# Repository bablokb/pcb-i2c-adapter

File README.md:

pcb-i2c-adapter
===============

This is a small PCB mapping various I2C pin combinations to a Grove connector.

Useful to connect all kinds of I2C-breakouts using Grove. Since every
breakout uses it's own pin-order, the PCB supports eight different
variations (additionally the Pi-variant: with 
pins 1 (3V3), 3 (SDA), 5 (SCL), 7 (nc), 9 (GND)).

KiCAD design-files are in the subdirectory `pcb-i2c-adapter`.

Production files for JLCPCB are in `production_files/`.

License
-------

[![CC BY-SA 4.0][cc-by-sa-shield]][cc-by-sa]

This work is licensed under a
[Creative Commons Attribution-ShareAlike 4.0 International
License][cc-by-sa].

[![CC BY-SA 4.0][cc-by-sa-image]][cc-by-sa]

[cc-by-sa]: http://creativecommons.org/licenses/by-sa/4.0/
[cc-by-sa-image]: https://licensebuttons.net/l/by-sa/4.0/88x31.png
[cc-by-sa-shield]:
https://img.shields.io/badge/License-CC%20BY--SA%204.0-lightgrey.svg

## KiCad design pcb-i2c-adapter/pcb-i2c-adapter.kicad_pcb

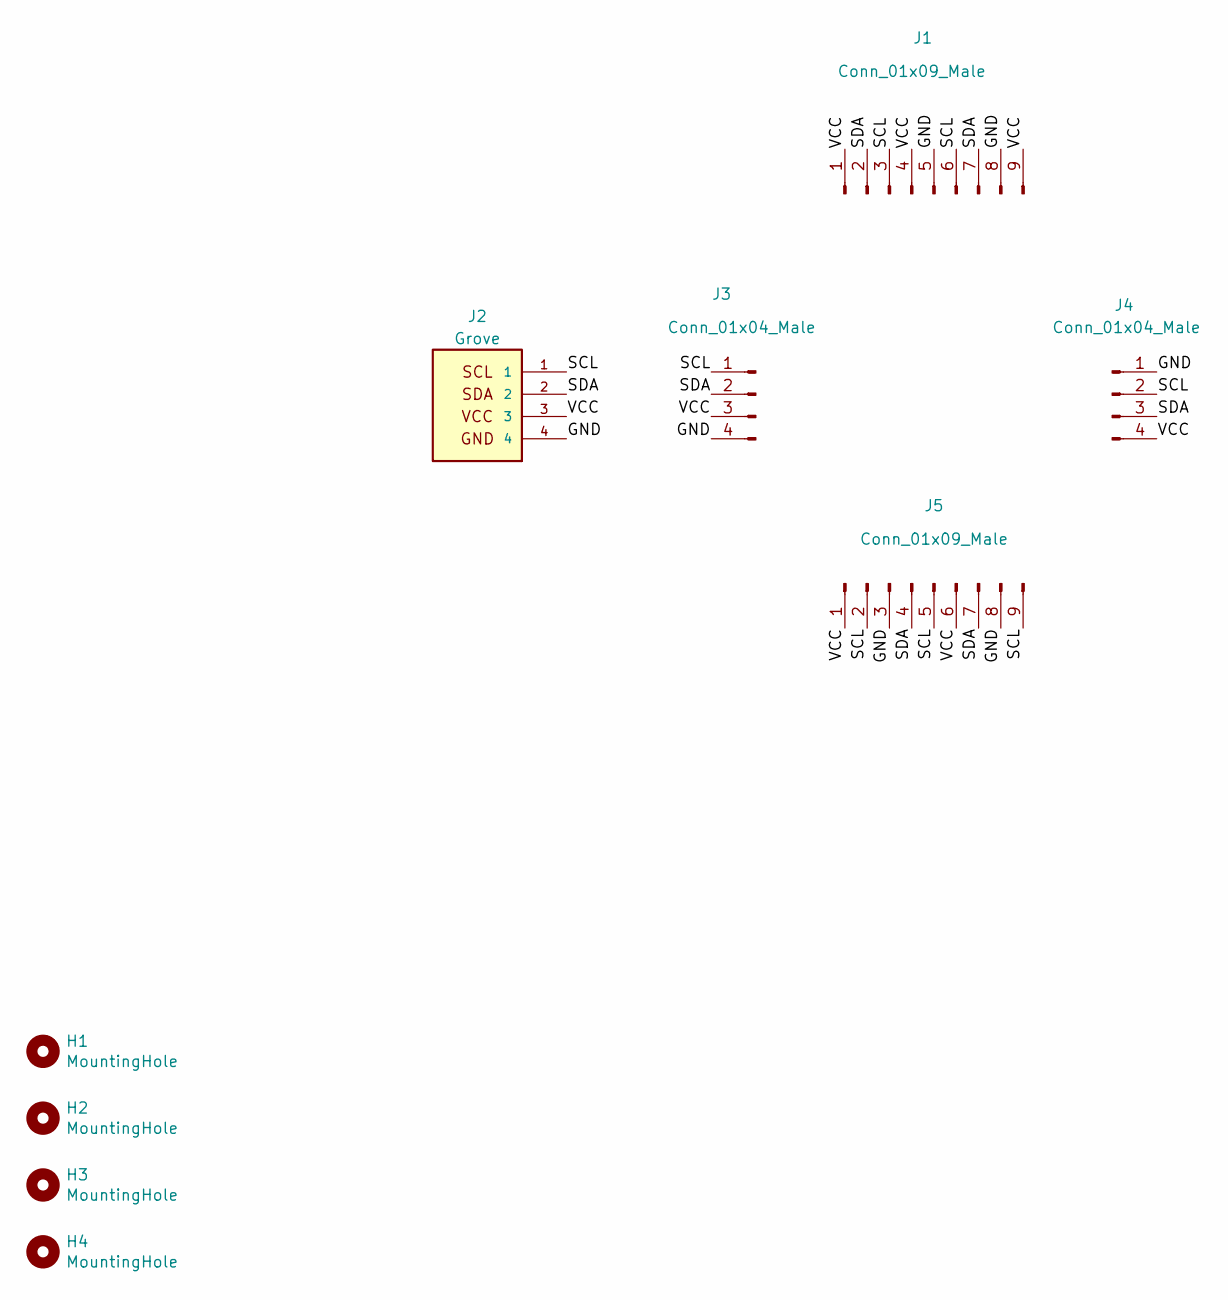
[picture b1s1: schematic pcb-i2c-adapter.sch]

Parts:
H1, H2, H3, H4: MountingHole; MountingHole_2.5mm
J1, J5: Conn_01x09_Male; Proto_Area_09x01
J2: Grove; grove_vertical
J3, J4: Conn_01x04_Male; Proto_Area_04x01

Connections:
/GND: J1.5, J1.8, J2.4, J3.4, J4.1, J5.3, J5.8
/SCL: J1.3, J1.6, J2.1, J3.1, J4.2, J5.2, J5.5, J5.9
/SDA: J1.2, J1.7, J2.2, J3.2, J4.3, J5.4, J5.7
/VCC: J1.1, J1.4, J1.9, J2.3, J3.3, J4.4, J5.1, J5.6

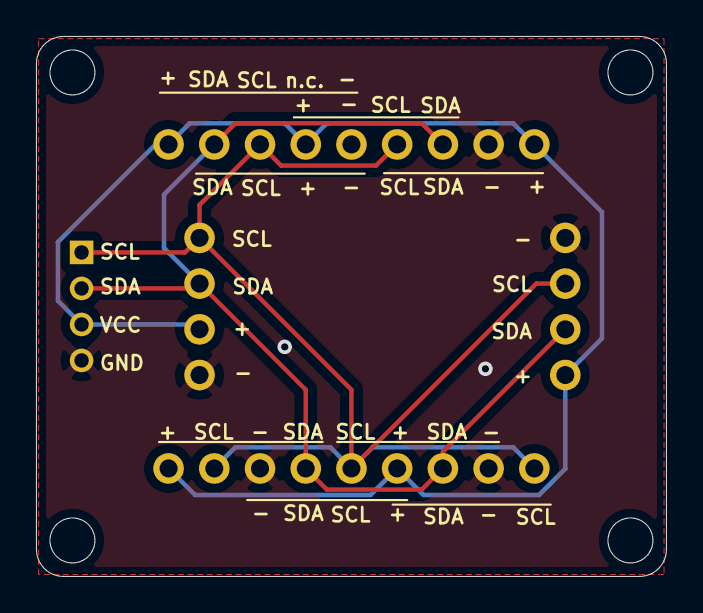
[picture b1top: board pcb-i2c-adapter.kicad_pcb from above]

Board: 2 copper layers, 35.0 x 30.0 mm, 9 parts (1 on the bottom side), 4 nets.

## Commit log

2022-01-08 added label for Pi-pinout
2022-01-12 updated config for gerber/drills
2023-02-26 add note about production files
